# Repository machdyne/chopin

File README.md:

# Chopin Motherboard

Chopin is a host board that when paired with a [Sechzig](https://github.com/machdyne/sechzig) compute module can function as a development board.

This repo contains schematics, PCB layouts, pinouts and documentation.

Find more information on the [Chopin product page](https://machdyne.com/product/chopin-motherboard/).

## Using Chopin

Chopin requires a Sechzig module to function. **When inserting a Sechzig module, make sure that pin 2 on Chopin and pin 2 on the module are both on the same side.**

## Programming

Chopin has a JTAG header that when paired with a JTAG programmer, can be used to program Sechzig modules. The following examples assume you're using a USB Blaster JTAG programmer.

Program the configuration SRAM of a Sechzig module:

```
sudo openFPGALoader -c usb-blaster image.bit
```

Program the configuration flash on a Sechzig module:

```
sudo openFPGALoader -f -c usb-blaster image.bit
```

## Pinouts

### JTAG Header

The 3.3V JTAG header can be used to program the Sechzig module. It can also be used to provide power (5V) to the board.

```
6 5
4 3
2 1
```

| Pin | Signal |
| --- | ------ |
| 1 | TCK |
| 2 | TDI |
| 3 | TDO |
| 4 | TMS |
| 5 | 5V0 |
| 6 | GND |

### LVDS Port

Chopin has an experimental SATA-style LVDS port. SATA is not supported.

| Pin | Signal |
| --- | ------ |
| 1 | GND |
| 2 | DS2\_P |
| 3 | DS2\_N |
| 4 | GND |
| 5 | DS1\_P |
| 6 | DS1\_N |
| 7 | GND |

## Funding

This project was partially funded through the NGI0 Entrust Fund, a fund established by NLnet with financial support from the European Commission's Next Generation Internet programme.

## License

This project is released under the [CERN-OHL-P](LICENSE.txt) license.

Note: You can use these designs for commercial purposes but we ask that instead of producing exact clones, that you either replace our trademarks and logos with your own or add your own next to ours.

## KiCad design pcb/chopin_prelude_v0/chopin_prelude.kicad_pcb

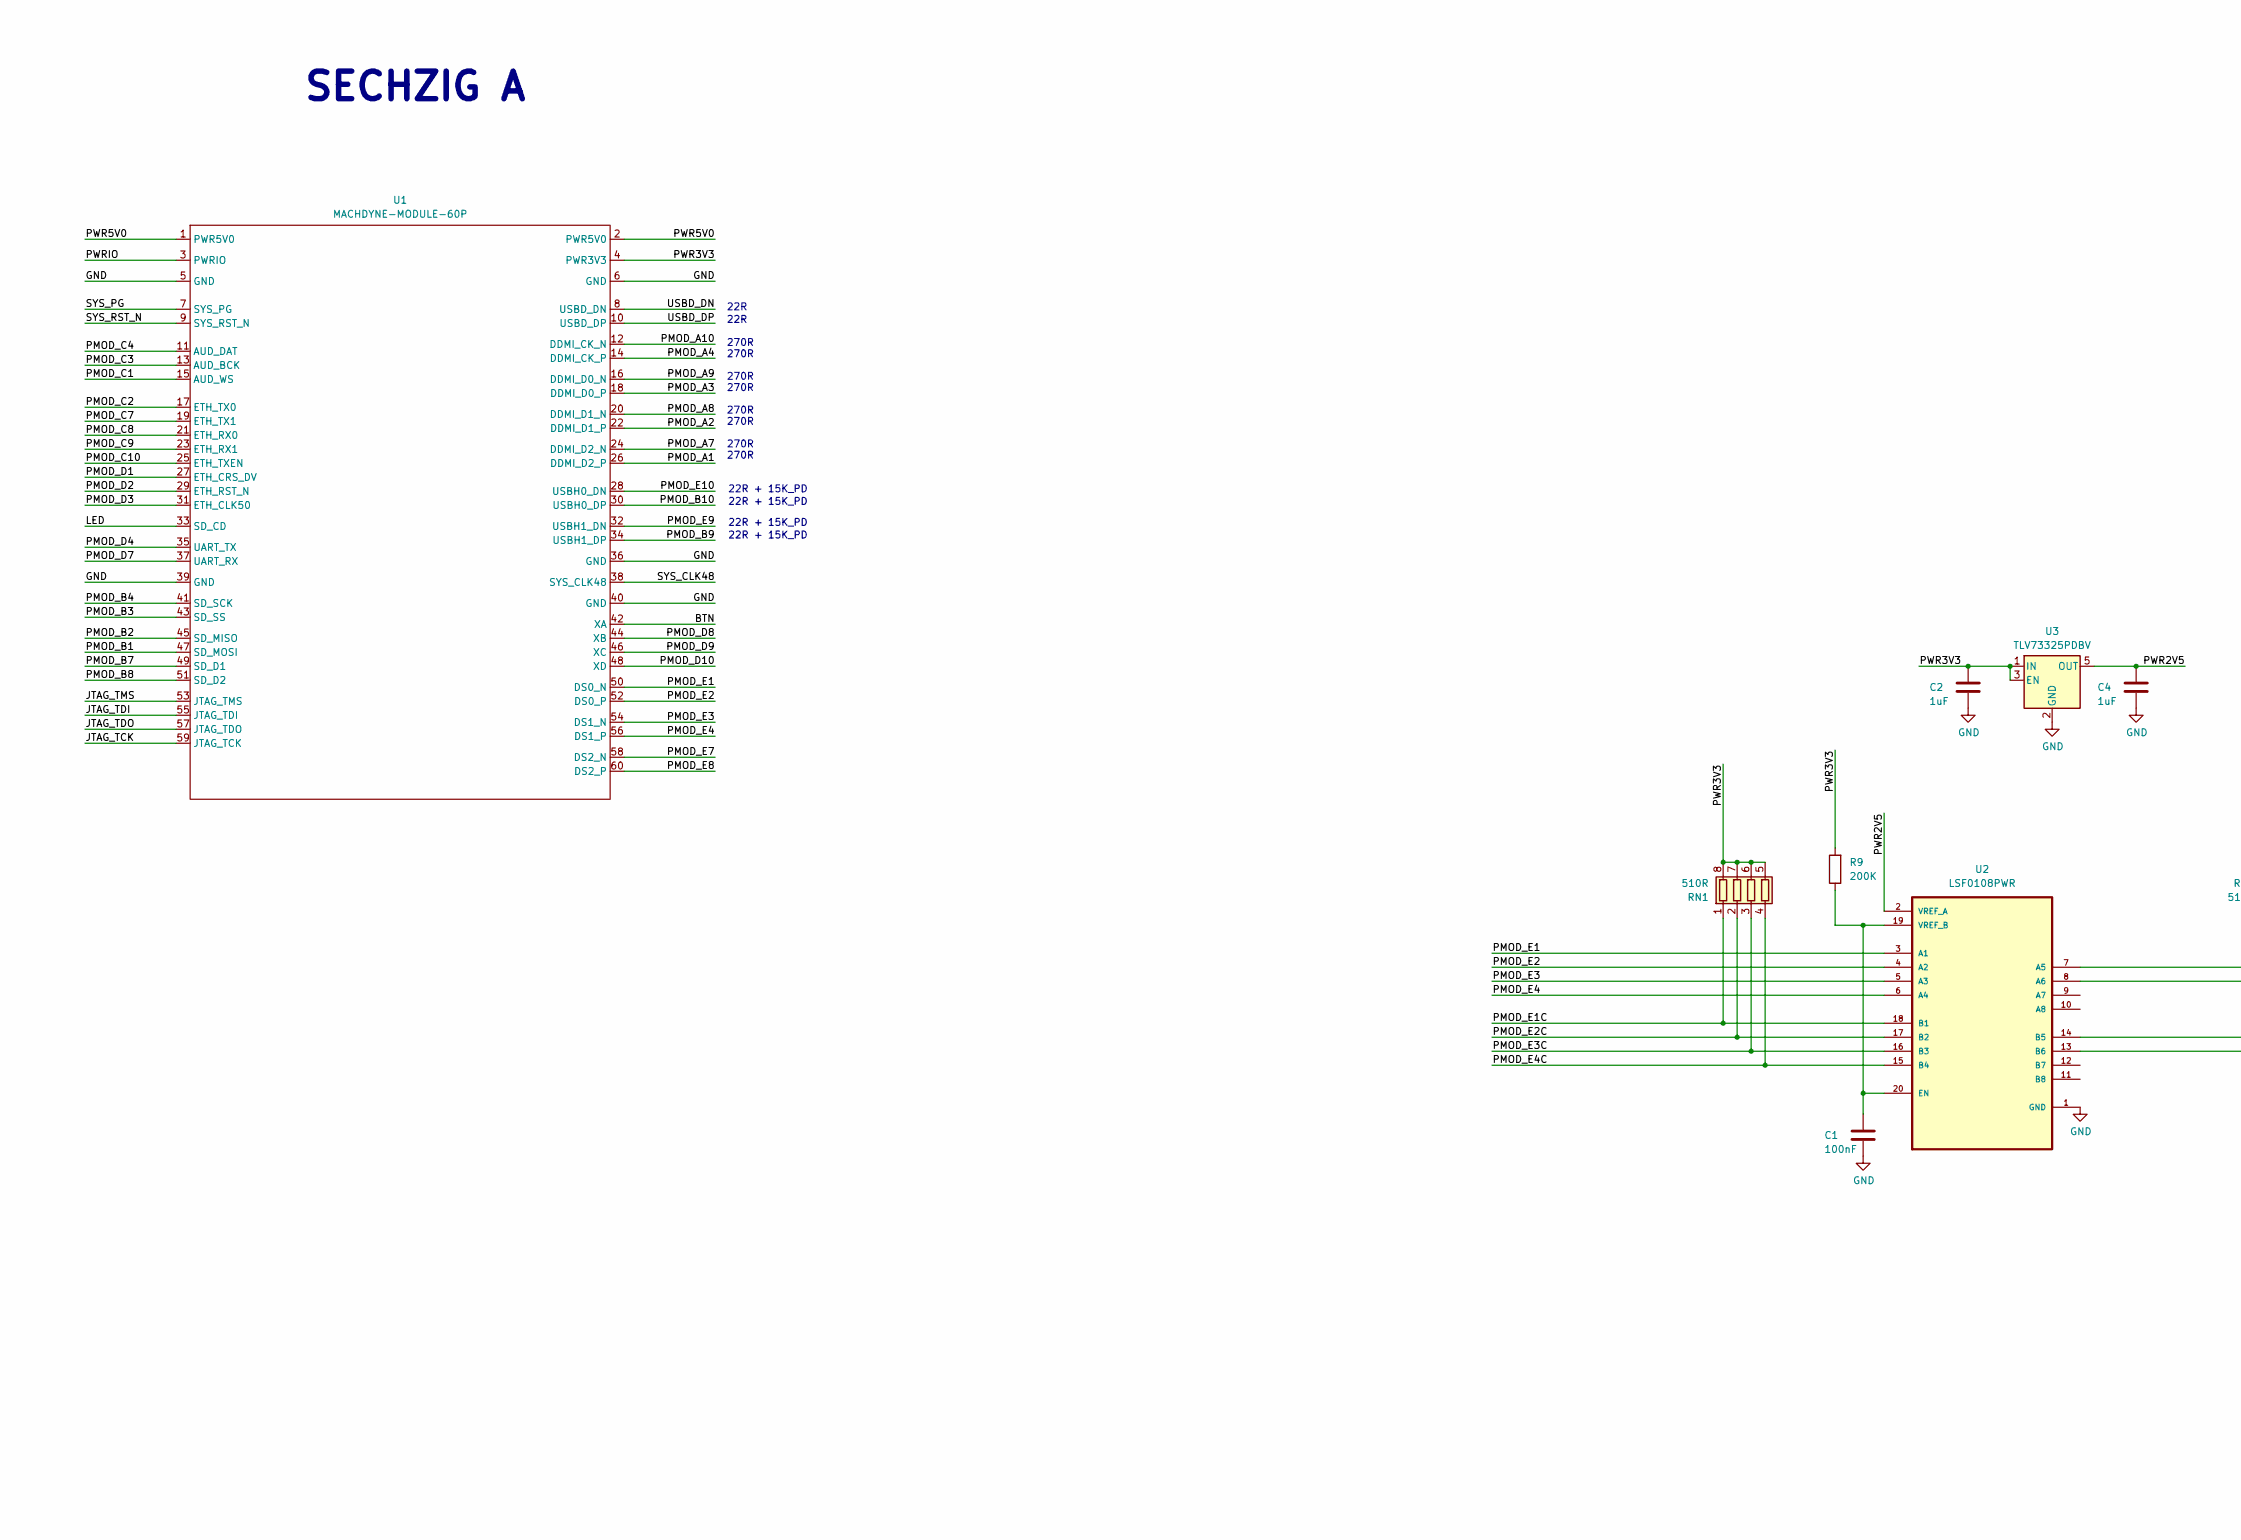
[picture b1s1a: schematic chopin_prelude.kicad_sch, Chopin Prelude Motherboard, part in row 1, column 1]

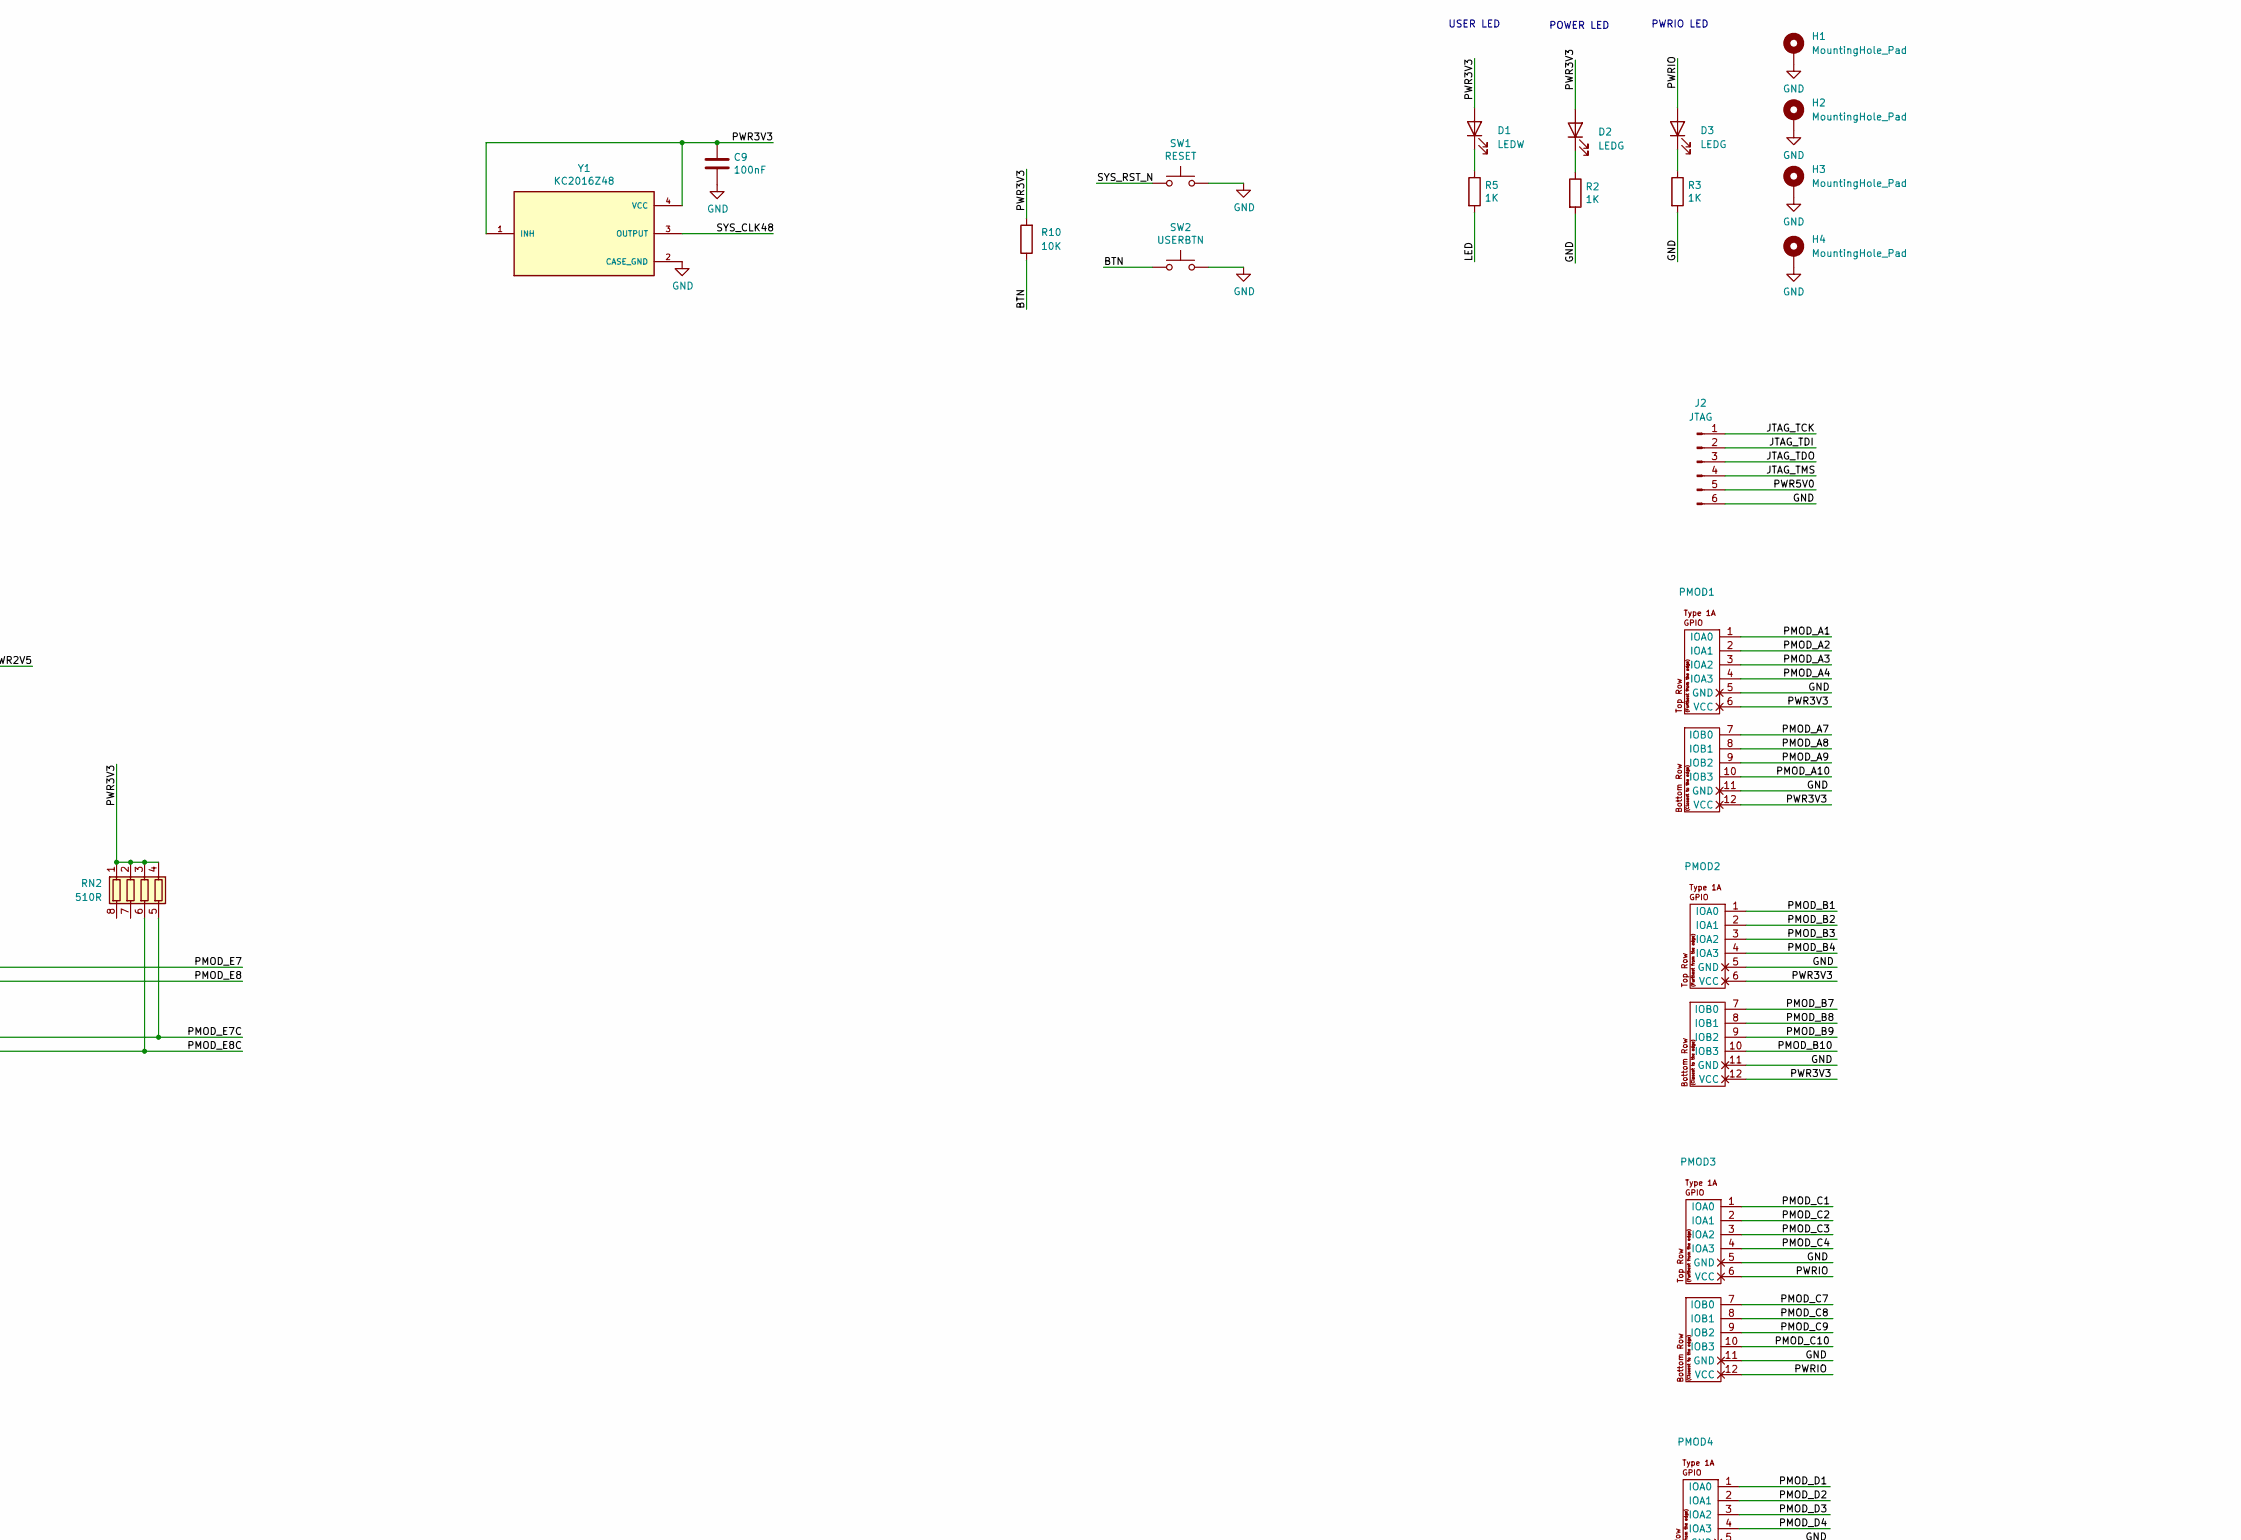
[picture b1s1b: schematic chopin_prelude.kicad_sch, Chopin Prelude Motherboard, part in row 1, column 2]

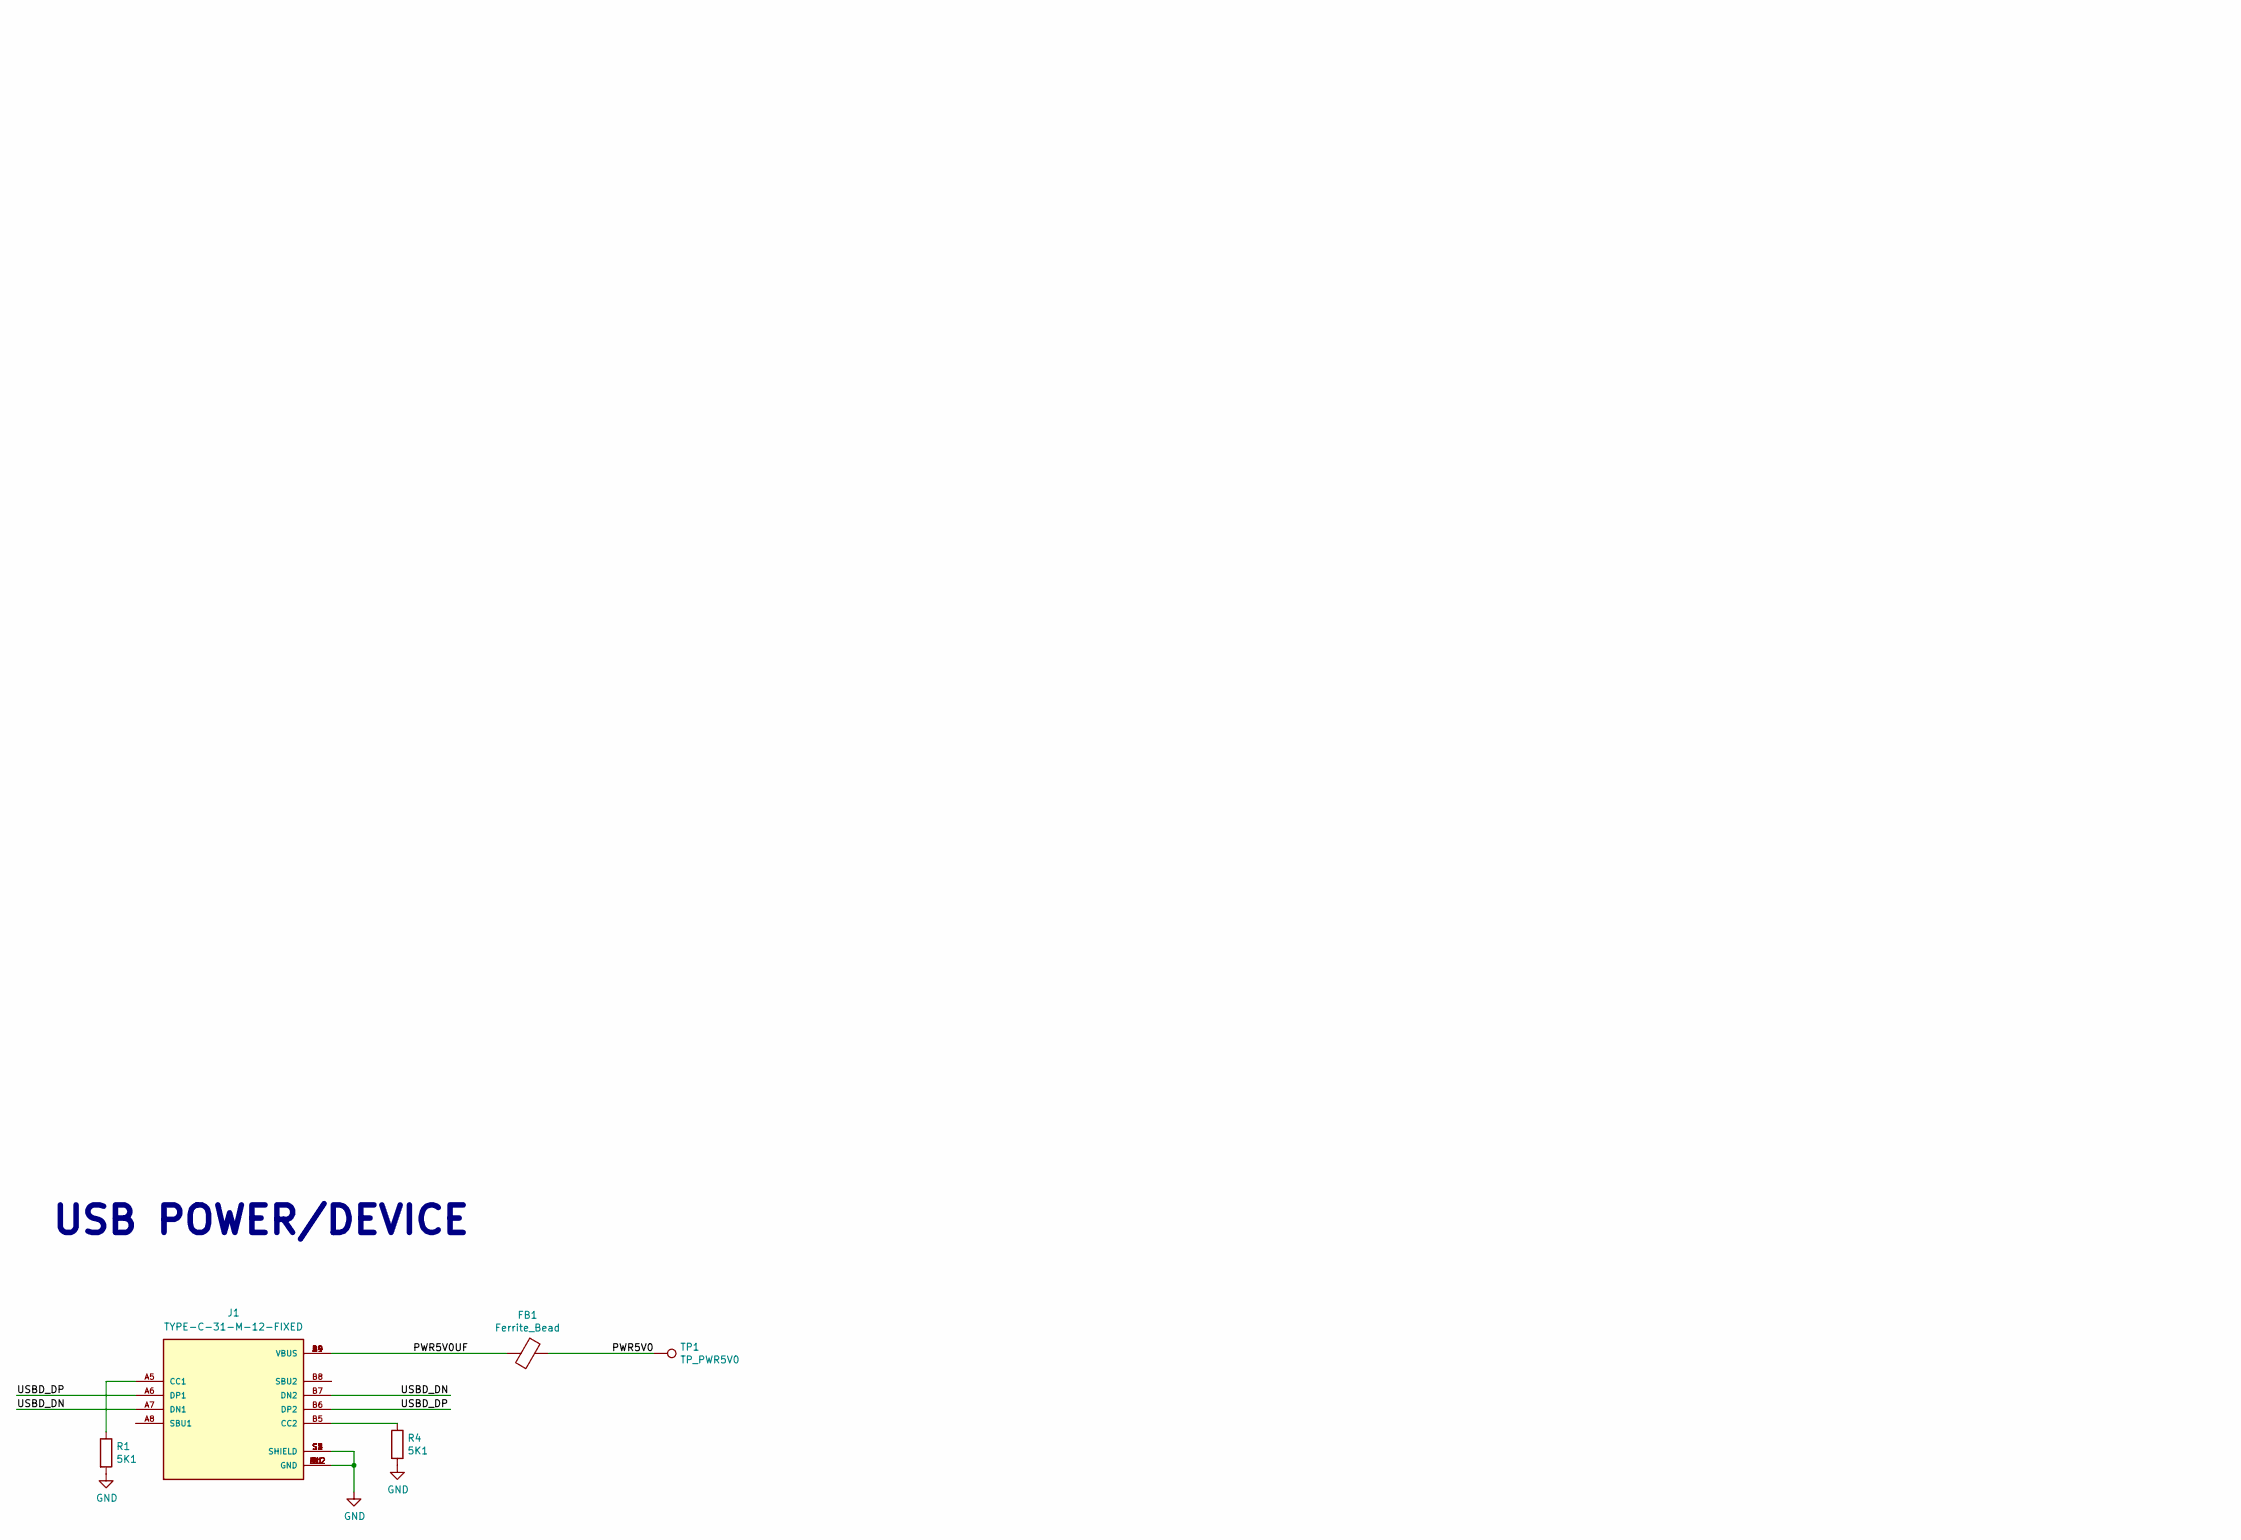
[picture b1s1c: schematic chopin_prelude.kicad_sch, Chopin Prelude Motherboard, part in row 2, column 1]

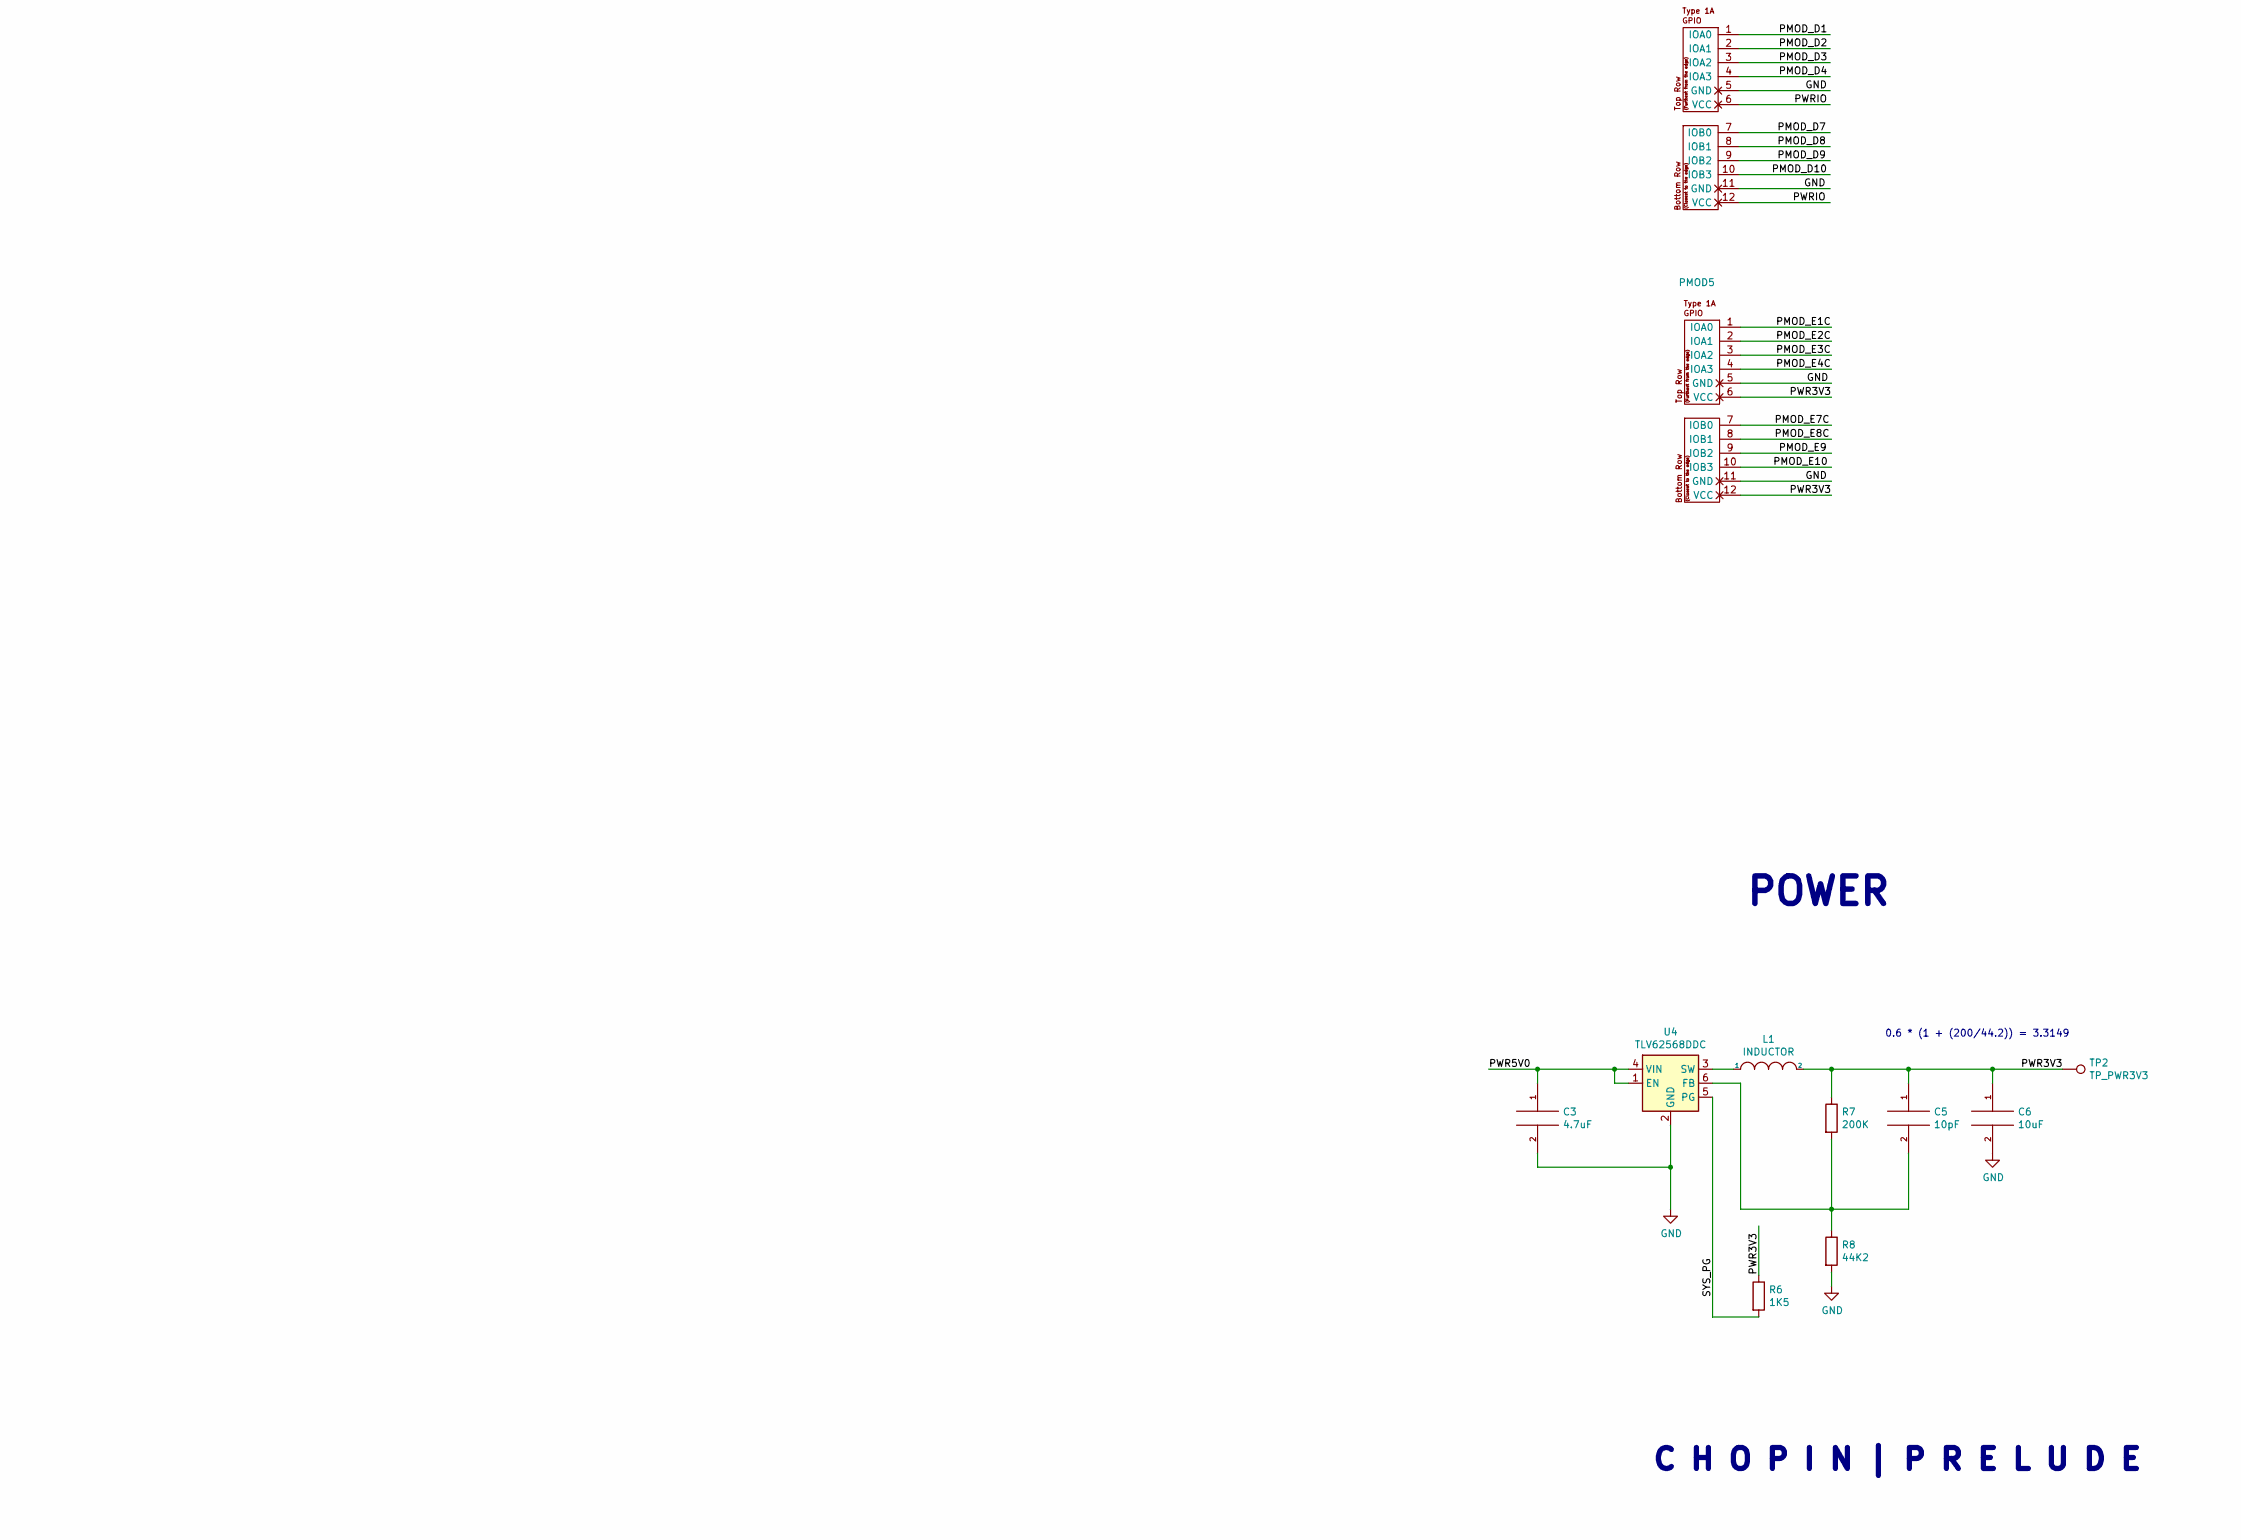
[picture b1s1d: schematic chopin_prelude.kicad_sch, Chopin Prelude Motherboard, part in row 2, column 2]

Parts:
C1: 100nF; C_0402_1005Metric
C2, C4: 1uF; C_0402_1005Metric
C3: 4.7uF; C_0603_1608Metric
C5: 10pF; C_0603_1608Metric
C6: 10uF; C_0603_1608Metric
C9: 100nF; C_0603_1608Metric
D1: LEDW; LED_0603_1608Metric
D2, D3: LEDG; LED_0603_1608Metric
FB1: Ferrite_Bead; R_0603_1608Metric
H1, H2, H3, H4: MountingHole_Pad; MountingHole_3.2mm_M3_Pad
J1: TYPE-C-31-M-12-FIXED; USB_C_Receptacle_HRO_TYPE-C-31-M-12-BIG-PADS; PARTREV A
J2: JTAG; PinHeader_2x03_P2.54mm_Vertical
L1: INDUCTOR; L_0805_2012Metric
PMOD1, PMOD2, PMOD5: PMOD-Device-x2-Type-1A-GPIO; PMOD_2x06_HOST
PMOD3, PMOD4: PMOD-Device-x2-Type-1A-GPIO; PMOD_2x06_HOST_VERTICAL
R1, R4: 5K1; R_0603_1608Metric
R2, R3, R5: 1K; R_0603_1608Metric
R6: 1K5; R_0603_1608Metric
R7: 200K; R_0603_1608Metric
R8: 44K2; R_0603_1608Metric
R9: 200K; R_0402_1005Metric
R10: 10K; R_0603_1608Metric
RN1, RN2: 510R; R_Array_Convex_4x0402
SW1: RESET; Button_2P_3x4mm
SW2: USERBTN; Kailh_Mute_6x6mm
TP1: TP_PWR5V0; TestPoint_THTPad_D1.0mm_Drill0.5mm
TP2: TP_PWR3V3; TestPoint_THTPad_D1.0mm_Drill0.5mm
U1: MACHDYNE-MODULE-60P; MACHDYNE_EDGE_SOCKET_60P
U2: LSF0108PWR; TSSOP-20_4.4x6.5mm_P0.65mm
U3: TLV73325PDBV; SOT-23-5
U4: TLV62568DDC; SOT-23-6
Y1: KC2016Z48; OSC_KC2016Z13.5600C1KX00; PARTREV November 2020

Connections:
/BTN: R10.1, SW2.1, U1.42 (XA)
/JTAG_TCK: J2.1, U1.59 (JTAG_TCK)
/JTAG_TDI: J2.2, U1.55 (JTAG_TDI)
/JTAG_TDO: J2.3, U1.57 (JTAG_TDO)
/JTAG_TMS: J2.4, U1.53 (JTAG_TMS)
/LED: R5.2, U1.33 (SD_CD)
/PMOD_A1: PMOD1.1 (IOA0), U1.26 (DDMI_D2_P)
/PMOD_A2: PMOD1.2 (IOA1), U1.22 (DDMI_D1_P)
/PMOD_A3: PMOD1.3 (IOA2), U1.18 (DDMI_D0_P)
/PMOD_A4: PMOD1.4 (IOA3), U1.14 (DDMI_CK_P)
/PMOD_A7: PMOD1.7 (IOB0), U1.24 (DDMI_D2_N)
/PMOD_A8: PMOD1.8 (IOB1), U1.20 (DDMI_D1_N)
/PMOD_A9: PMOD1.9 (IOB2), U1.16 (DDMI_D0_N)
/PMOD_A10: PMOD1.10 (IOB3), U1.12 (DDMI_CK_N)
/PMOD_B1: PMOD2.1 (IOA0), U1.47 (SD_MOSI)
/PMOD_B2: PMOD2.2 (IOA1), U1.45 (SD_MISO)
/PMOD_B3: PMOD2.3 (IOA2), U1.43 (SD_SS)
/PMOD_B4: PMOD2.4 (IOA3), U1.41 (SD_SCK)
/PMOD_B7: PMOD2.7 (IOB0), U1.49 (SD_D1)
/PMOD_B8: PMOD2.8 (IOB1), U1.51 (SD_D2)
/PMOD_B9: PMOD2.9 (IOB2), U1.34 (USBH1_DP)
/PMOD_B10: PMOD2.10 (IOB3), U1.30 (USBH0_DP)
/PMOD_C1: PMOD3.1 (IOA0), U1.15 (AUD_WS)
/PMOD_C2: PMOD3.2 (IOA1), U1.17 (ETH_TX0)
/PMOD_C3: PMOD3.3 (IOA2), U1.13 (AUD_BCK)
/PMOD_C4: PMOD3.4 (IOA3), U1.11 (AUD_DAT)
/PMOD_C7: PMOD3.7 (IOB0), U1.19 (ETH_TX1)
/PMOD_C8: PMOD3.8 (IOB1), U1.21 (ETH_RX0)
/PMOD_C9: PMOD3.9 (IOB2), U1.23 (ETH_RX1)
/PMOD_C10: PMOD3.10 (IOB3), U1.25 (ETH_TXEN)
/PMOD_D1: PMOD4.1 (IOA0), U1.27 (ETH_CRS_DV)
/PMOD_D2: PMOD4.2 (IOA1), U1.29 (ETH_RST_N)
/PMOD_D3: PMOD4.3 (IOA2), U1.31 (ETH_CLK50)
/PMOD_D4: PMOD4.4 (IOA3), U1.35 (UART_TX)
/PMOD_D7: PMOD4.7 (IOB0), U1.37 (UART_RX)
/PMOD_D8: PMOD4.8 (IOB1), U1.44 (XB)
/PMOD_D9: PMOD4.9 (IOB2), U1.46 (XC)
/PMOD_D10: PMOD4.10 (IOB3), U1.48 (XD)
/PMOD_E1: U1.50 (DS0_N), U2.3 (A1)
/PMOD_E1C: PMOD5.1 (IOA0), RN1.1 (R1.1), U2.18 (B1)
/PMOD_E2: U1.52 (DS0_P), U2.4 (A2)
/PMOD_E2C: PMOD5.2 (IOA1), RN1.2 (R2.1), U2.17 (B2)
/PMOD_E3: U1.54 (DS1_N), U2.5 (A3)
/PMOD_E3C: PMOD5.3 (IOA2), RN1.3 (R3.1), U2.16 (B3)
/PMOD_E4: U1.56 (DS1_P), U2.6 (A4)
/PMOD_E4C: PMOD5.4 (IOA3), RN1.4 (R4.1), U2.15 (B4)
/PMOD_E7: U1.58 (DS2_N), U2.7 (A5)
/PMOD_E7C: PMOD5.7 (IOB0), RN2.5 (R4.2), U2.14 (B5)
/PMOD_E8: U1.60 (DS2_P), U2.8 (A6)
/PMOD_E8C: PMOD5.8 (IOB1), RN2.6 (R3.2), U2.13 (B6)
/PMOD_E9: PMOD5.9 (IOB2), U1.32 (USBH1_DN)
/PMOD_E10: PMOD5.10 (IOB3), U1.28 (USBH0_DN)
/PWR2V5: C4.1, U2.2 (VREF_A), U3.5 (OUT)
/PWR3V3: C2.1, C5.1, C6.1, C9.1, D1.2 (A), D2.2 (A), L1.2, PMOD1.6 (VCC), PMOD1.12 (VCC), PMOD2.6 (VCC), PMOD2.12 (VCC), PMOD5.6 (VCC), PMOD5.12 (VCC), R6.1, R7.1, R9.2, R10.2, RN1.5 (R4.2), RN1.6 (R3.2), RN1.7 (R2.2), RN1.8 (R1.2), RN2.1 (R1.1), RN2.2 (R2.1), RN2.3 (R3.1), RN2.4 (R4.1), TP2.1, U1.4 (PWR3V3), U3.1 (IN), U3.3 (EN), Y1.1 (INH), Y1.4 (VCC)
/PWR5V0: C3.1, FB1.1, J2.5, TP1.1, U1.1 (PWR5V0), U1.2 (PWR5V0), U4.1 (EN), U4.4 (VIN)
/PWR5V0UF: FB1.2, J1.A4 (VBUS), J1.A9 (VBUS), J1.B4 (VBUS), J1.B9 (VBUS)
/PWRIO: D3.2 (A), PMOD3.6 (VCC), PMOD3.12 (VCC), PMOD4.6 (VCC), PMOD4.12 (VCC), U1.3 (PWRIO)
/SYS_CLK48: U1.38 (SYS_CLK48), Y1.3 (OUTPUT)
/SYS_PG: R6.2, U1.7 (SYS_PG), U4.5 (PG)
/SYS_RST_N: SW1.1, U1.9 (SYS_RST_N)
/USBD_DN: J1.A7 (DN1), J1.B7 (DN2), U1.8 (USBD_DN)
/USBD_DP: J1.A6 (DP1), J1.B6 (DP2), U1.10 (USBD_DP)
GND: C1.2, C2.2, C3.2, C4.2, C6.2, C9.2, H1.1, H2.1, H3.1, H4.1, J1.A1 (GND), J1.A12 (GND), J1.B1 (GND), J1.B12 (GND), J1.S1 (SHIELD), J1.S2 (SHIELD), J1.S3 (SHIELD), J1.S4 (SHIELD), J2.6, PMOD1.5 (GND), PMOD1.11 (GND), PMOD2.5 (GND), PMOD2.11 (GND), PMOD3.5 (GND), PMOD3.11 (GND), PMOD4.5 (GND), PMOD4.11 (GND), PMOD5.5 (GND), PMOD5.11 (GND), R1.2, R2.2, R3.2, R4.2, R8.2, SW1.2, SW2.2, U1.5 (GND), U1.6 (GND), U1.36 (GND), U1.39 (GND), U1.40 (GND), U2.1 (GND), U3.2 (GND), U4.2 (GND), Y1.2 (CASE_GND)
unnamed: D1.1 (K), R5.1
unnamed: D2.1 (K), R2.1
unnamed: D3.1 (K), R3.1
unnamed: J1.A5 (CC1), R1.1
unnamed: J1.B5 (CC2), R4.1
unnamed: C1.1, R9.1, U2.19 (VREF_B), U2.20 (EN)
unnamed: C5.2, R7.2, R8.1, U4.6 (FB)
unnamed: L1.1, U4.3 (SW)

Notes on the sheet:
PWRIO LED
C H O P I N | P R E L U D E
0.6 * (1 + (200/44.2)) = 3.3149
USER LED
22R + 15K_PD
22R
POWER
SECHZIG A
POWER LED
270R 270R 270R 270R 270R 270R 270R 270R
USB POWER/DEVICE

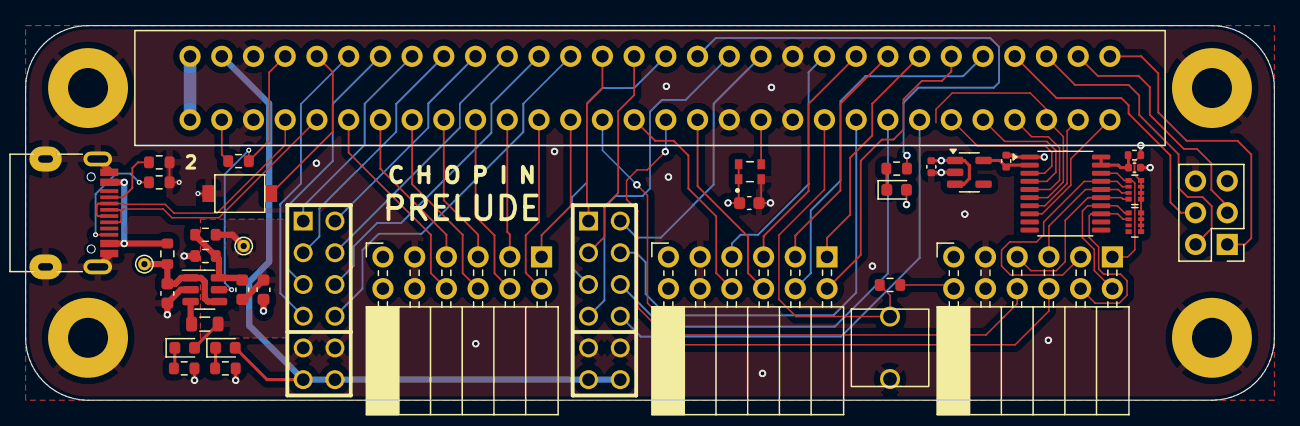
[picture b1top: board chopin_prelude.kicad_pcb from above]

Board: 4 copper layers, 100.0 x 30.0 mm, 44 parts (0 on the bottom side), 71 nets.

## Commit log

2024-02-15 add image
2024-02-17 fix swapped pins
2024-03-19 update license
2024-11-05 add chopin+ml3 blinky
2025-05-12 add prelude lpf
2025-05-12 add prelude pcb

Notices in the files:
pcb/chopin_prelude_v0/chopin_prelude.kicad_sch:
Copyright © 2025 Lone Dynamics Corporation
